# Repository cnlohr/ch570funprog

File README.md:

# ch570funprog

Project Status: It works, in a pinch, but hardware and software is still evolving.

CH570-based programmer for CH32 microcontrollers.

## Firmware

Firmware uses common funprog logic that now lives in [ch32fun/minichlink/funprog](ch32fun/minichlink/funprog). Any updates to functionality and protocol should be updated via ch32fun submodule. Consult [README](ch32fun/minichlink/funprog/README.md) about available configurations.

Firmware creates CDC ACM device on the connected host that can be used either for debugging purposes or as CDC-UART adapter. In the latter case it will use ``SWD`` pin as ``UART RX`` and ``SWC`` pin as ``UART TX``, for the first version of the hardware. On the second revision, there are dedicated UART pins on the header, and they will be used instead.

To switch UART on and off (and toggle functionality of SWD pins on the first revision boards) you need to send a Vendor Command using minichlink like this:

``./minichlink -X u1`` (1/0 - turn UART on or off)

or

``./minichlink -X U1`` (turn UART on and save this setting to the flash)

To enable debug prints in this firmware set ``DEBUG_PRINT`` in [funprog_config.h](firmware/funprog_config.h) to 1. Also define hardware version there, this will affect UART related functions.

### Hardware Note

* You must connect an external 1.5k to 10k pull-up resistor between SWIO and VDD

### General Game Plan

- [x] Be a cheap, minichlink-compatible programmer programming over USB
- [x] Test on ch32v00x for SWIO mode (and tune)
- [ ] Test on more boards (And tune SWD)
- [ ] Be a iSLER gateway.
- [ ] Enable flashing of slave processors over iSLER.
- [ ] Enable self-program over iSLER

### Some Developer Notes

* To force-enter ISP (bootloader) mode, hold D+ high.
* You will need to `minichlink -P` to enable writing to the 570.

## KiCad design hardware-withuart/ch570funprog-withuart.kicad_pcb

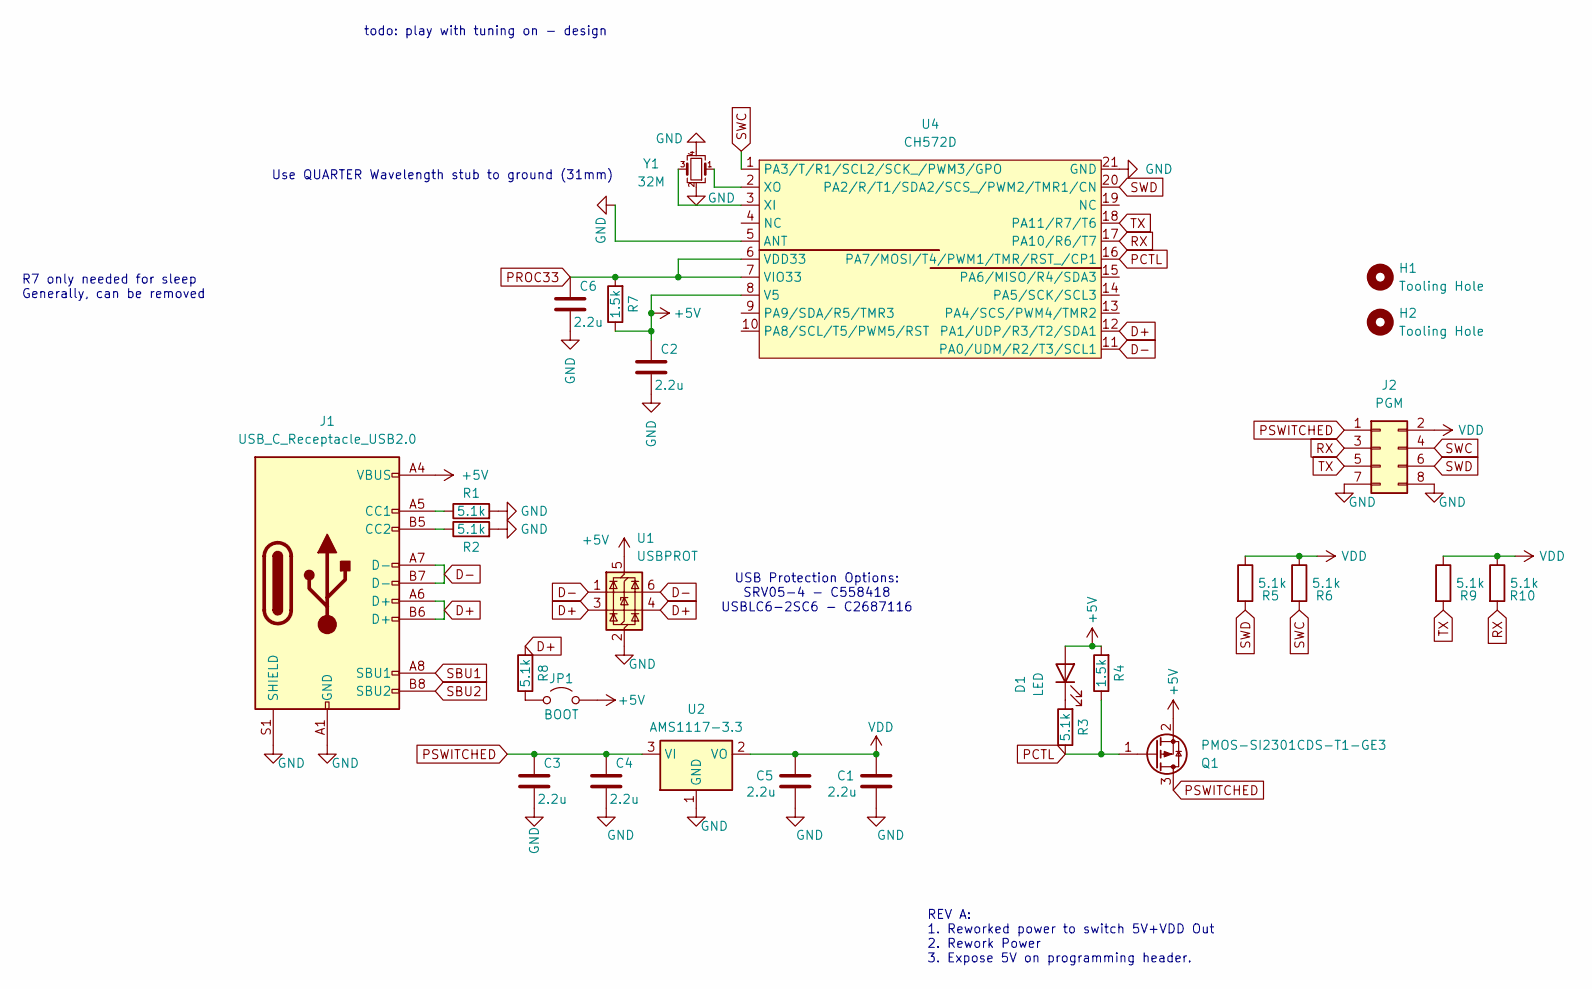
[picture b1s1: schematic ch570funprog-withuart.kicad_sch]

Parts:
C1, C2, C3, C4, C5, C6: 2.2u; R_0402_1005Metric; LCSC C12530
D1: LED; LED_0603_1608Metric; LCSC C2286
H1, H2: Tooling Hole; ToolingHole_JLCPCB
J1: USB_C_Receptacle_USB2.0; USB_C_MOD_Receptacle_HRO_TYPE-C-31-M-12; LCSC C2765186
J2: PGM; EDGE_02x04_2.54mm
JP1: BOOT; SolderJumper-2_P1.3mm_Open_TrianglePad1.0x1.5mm
Q1: PMOS-SI2301CDS-T1-GE3; SOT-23; LCSC C10487
R1, R2, R3, R5, R6, R8, R9, R10: 5.1k; R_0402_1005Metric; LCSC C25905
R4, R7: 1.5k; R_0402_1005Metric; LCSC C25867
U1: USBPROT; SOT-23-6; LCSC C558418
U2: AMS1117-3.3; SOT-223-3_TabPin2; LCSC C6186
U4: CH572D; QFN-20-1EP_3x3mm_P0.4mm_EP1.65x1.65mm; LCSC C46597863
Y1: 32M; Crystal_SMD_2016-4Pin_2.0x1.6mm; LCSC C718072

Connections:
+5V: C2.2, D1.2 (A), J1.A4 (VBUS), J1.A9 (VBUS), J1.B4 (VBUS), J1.B9 (VBUS), JP1.2 (B), Q1.2 (S), R4.2, R7.1, U1.5 (VBUS), U4.8 (V5)
D+: J1.A6 (D+), J1.B6 (D+), R8.2, U1.3 (I/O2), U1.4 (I/O2), U4.12 (PA1/UDP/R3/T2/SDA1)
D-: J1.A7 (D-), J1.B7 (D-), U1.1 (I/O1), U1.6 (I/O1), U4.11 (PA0/UDM/R2/T3/SCL1)
GND: C1.1, C2.1, C3.1, C4.1, C5.1, C6.1, J1.A1 (GND), J1.A12 (GND), J1.B1 (GND), J1.B12 (GND), J1.S1 (SHIELD), J2.7, J2.8, R1.2, R2.2, U1.2 (GND), U2.1 (GND), U4.5 (ANT), U4.21 (GND), Y1.2, Y1.4
unnamed: D1.1 (K), R3.2
unnamed: J1.A5 (CC1), R1.1
unnamed: J1.B5 (CC2), R2.1
unnamed: JP1.1 (A), R8.1
unnamed: U4.3 (XI), Y1.3
unnamed: U4.2 (XO), Y1.1
PCTL: Q1.1 (G), R3.1, R4.1, U4.16 (PA7/MOSI/T4/PWM1/TMR/RST_/CP1)
PROC33: C6.2, R7.2, U4.6 (VDD33), U4.7 (VIO33)
PSWITCHED: C3.2, C4.2, J2.1, Q1.3 (D), U2.3 (VI)
RX: J2.3, R10.2, U4.17 (PA10/R6/T7)
SBU1: J1.A8 (SBU1)
SBU2: J1.B8 (SBU2)
SWC: J2.4, R6.2, U4.1 (PA3/T/R1/SCL2/SCK_/PWM3/GPO)
SWD: J2.6, R5.2, U4.20 (PA2/R/T1/SDA2/SCS_/PWM2/TMR1/CN)
TX: J2.5, R9.2, U4.18 (PA11/R7/T6)
VDD: C1.2, C5.2, J2.2, R5.1, R6.1, R9.1, R10.1, U2.2 (VO)

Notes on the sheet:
REV A: 1. Reworked power to switch 5V+VDD Out 2. Rework Power 3. Expose 5V on programming header.
todo: play with tuning on - design
Use QUARTER Wavelength stub to ground (31mm)
USB Protection Options: SRV05-4 - C558418 USBLC6-2SC6 - C2687116
R7 only needed for sleep Generally, can be removed

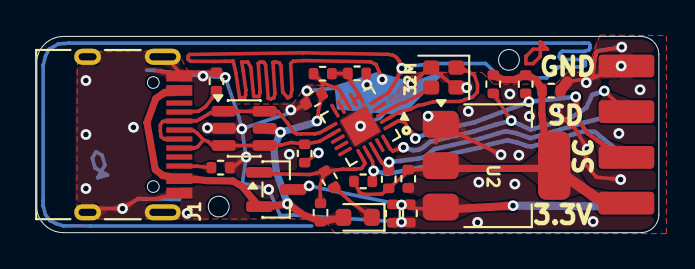
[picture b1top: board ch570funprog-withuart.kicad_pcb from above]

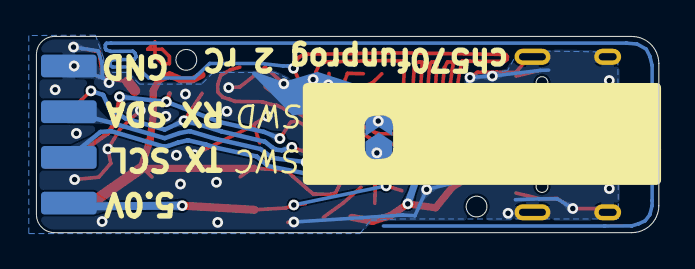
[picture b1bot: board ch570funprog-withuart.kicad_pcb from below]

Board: 2 copper layers, 34.6 x 10.9 mm, 27 parts (2 on the bottom side), 18 nets.

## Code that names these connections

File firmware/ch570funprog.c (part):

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#include "fsusb.h"
#include "flash_storage.h"

#define PIN_SWD              PA2
#define PIN_SWC              PA3

#define PIN_SWD_MASK         (1<<2)
#define PIN_SWC_MASK         (1<<3)

#define LED                  PA7
#define LED_ON_POLARITY      0
#define PIN_TARGETPOWER      PA7

#define POWER_ON_POLARITY    0
#define POWER_OFF_POLARITY   1
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#include "../ch32fun/minichlink/funprog/funprog_logic.h"

#if defined(HW_VERSION) && HW_VERSION==1
#define UART_TX_PIN          PA3
#define UART_RX_PIN          PA2
#else
#define UART_TX_PIN          PA11
#define UART_RX_PIN          PA10
#endif
// #define UART_DTR_PIN
#include "uart_cdc.h"
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
void setup_swdio_gpio()
{
	funDigitalWrite( PIN_SWD, 1 );
	funDigitalWrite( PIN_SWC, 1 );
	funPinMode( PIN_SWD, GPIO_CFGLR_OUT_10Mhz_PP );
	funPinMode( PIN_SWC, GPIO_CFGLR_OUT_10Mhz_PP );
}

void enable_uart( uint8_t on )
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
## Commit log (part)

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2026-06-01 Still not quite working
2026-06-01 bump firmware, getting closer
2026-06-02 Things seem closer.
2026-06-02 Bump.
2026-06-02 Updated readme + design
2026-06-02 Bump readme
2026-06-02 Update submodule
2026-06-03 Bump design and reorganize config location
2026-06-04 Update design
2026-06-16 Add freshflash for dealing with the IAP bootloader
2026-06-20 Forgot missed files
